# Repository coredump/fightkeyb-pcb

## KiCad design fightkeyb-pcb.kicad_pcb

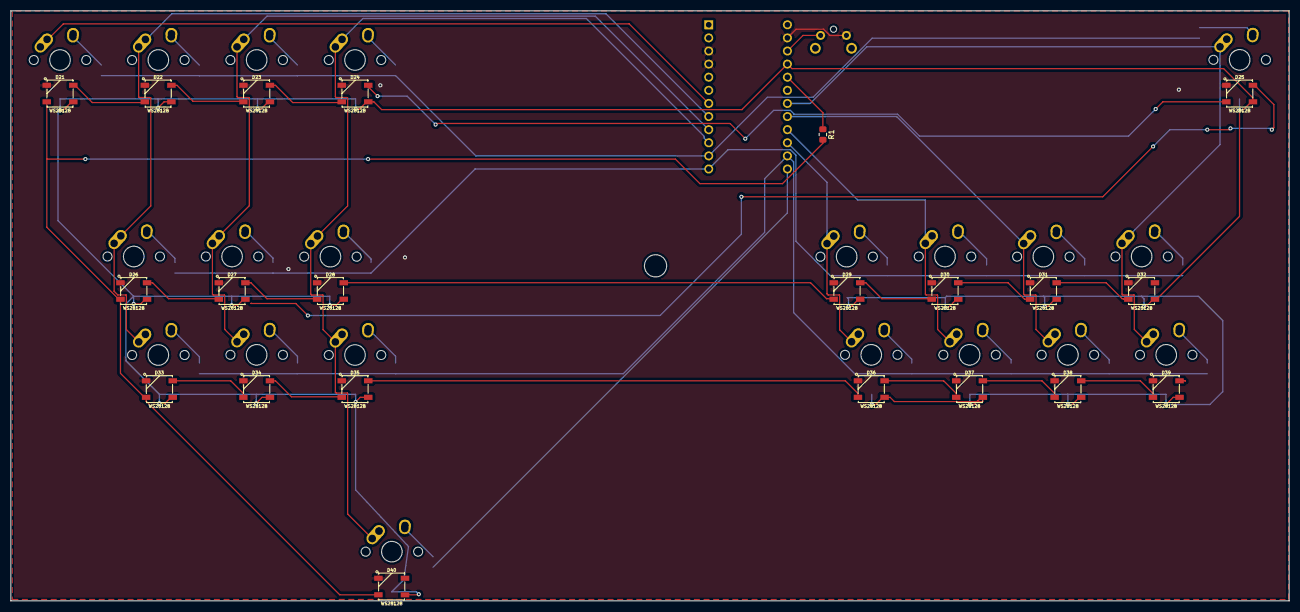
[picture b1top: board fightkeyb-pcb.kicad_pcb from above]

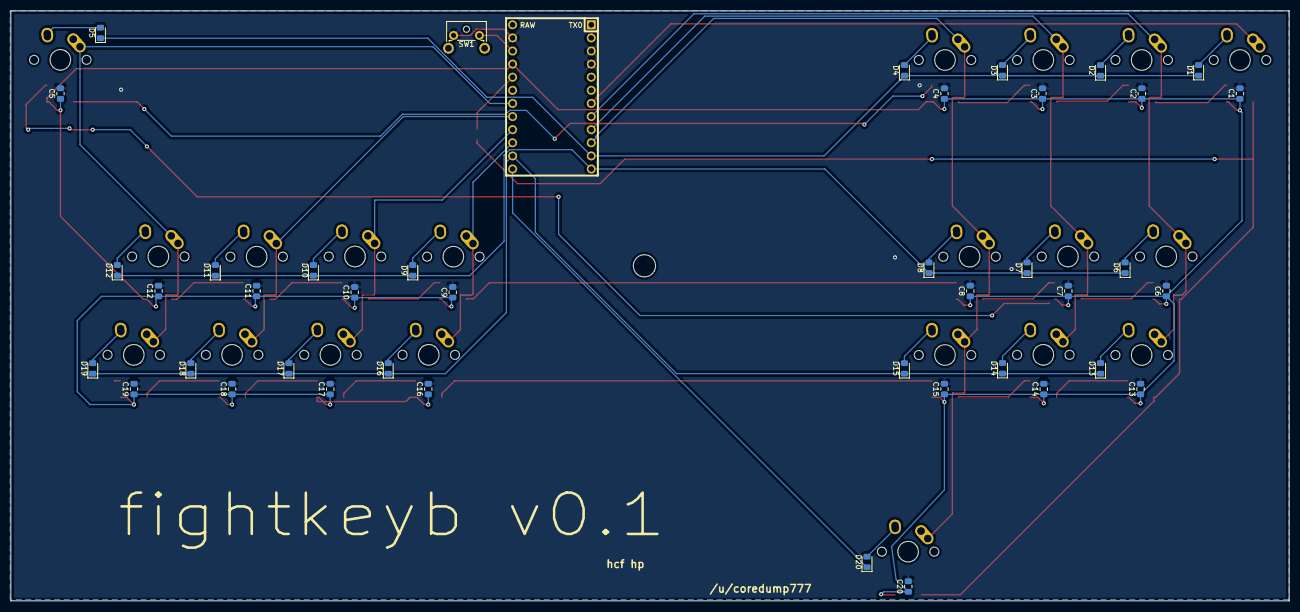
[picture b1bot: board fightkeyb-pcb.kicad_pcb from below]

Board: 2 copper layers, 247.6 x 114.3 mm, 83 parts (41 on the bottom side), 53 nets.

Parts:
C1, C2, C3, C4, C5, C6, C7, C8, C9, C10, C11, C12, C13, C14, C15, C16, C17, C18, C19, C20: 0u1; C_0805_2012Metric_Pad1.15x1.40mm_HandSolder
D1, D2, D3, D4, D5, D6, D7, D8, D9, D10, D11, D12, D13, D14, D15, D16, D17, D18, D19, D20: 1N4148; D_0805_2012Metric_Pad1.15x1.40mm_HandSolder
D21, D22, D23, D24, D25, D26, D27, D28, D29, D30, D31, D32, D33, D34, D35, D36, D37, D38, D39, D40: WS2812B
MX1, MX2, MX3, MX4, MX5, MX6, MX7, MX8, MX9, MX10, MX11, MX12, MX13, MX14, MX15, MX16, MX17, MX18, MX19, MX20: MX-1U; MX-1U-NoLED
R1: 330R; R_0805_2012Metric_Pad1.15x1.40mm_HandSolder
SW1: SW_SPST; SW_Tactile_SPST_Angled_MJTP1117
U1: ProMicro; ArduinoProMicro-BackSide

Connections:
/Led Matrix/DIN: R1.1, U1.20
/Led Matrix/GND: C1.2, C2.2, C3.2, C4.2, C5.2, C6.2, C7.2, C8.2, C9.2, C10.2, C11.2, C12.2, C13.2, C14.2, C15.2, C16.2, C17.2, C18.2, C19.2, C20.2, D21.3, D22.3, D23.3, D24.3, D25.3, D26.3, D27.3, D28.3, D29.3, D30.3, D31.3, D32.3, D33.3, D34.3, D35.3, D36.3, D37.3, D38.3, D39.3, D40.3, SW1.1, U1.3, U1.4, U1.23
/Led Matrix/VCC: C1.1, C2.1, C3.1, C4.1, C5.1, C6.1, C7.1, C8.1, C9.1, C10.1, C11.1, C12.1, C13.1, C14.1, C15.1, C16.1, C17.1, C18.1, C19.1, C20.1, D21.1, D22.1, D23.1, D24.1, D25.1, D26.1, D27.1, D28.1, D29.1, D30.1, D31.1, D32.1, D33.1, D34.1, D35.1, D36.1, D37.1, D38.1, D39.1, D40.1, U1.21
unnamed: D1.1, D2.1, D3.1, D4.1, D5.1, U1.11
unnamed: D1.2, MX1.2
unnamed: D2.2, MX2.2
unnamed: D3.2, MX3.2
unnamed: D4.2, MX4.2
unnamed: D5.2, MX5.2
unnamed: D6.2, MX6.2
unnamed: D7.2, MX7.2
unnamed: D8.2, MX8.2
unnamed: D9.2, MX9.2
unnamed: D6.1, D7.1, D8.1, D9.1, D10.1, D11.1, D12.1, U1.12
unnamed: D10.2, MX10.2
unnamed: D11.2, MX11.2
unnamed: D12.2, MX12.2
unnamed: D13.1, D14.1, D15.1, D16.1, D17.1, D18.1, D19.1, U1.14
unnamed: D13.2, MX13.2
unnamed: D14.2, MX14.2
unnamed: D15.2, MX15.2
unnamed: D16.2, MX16.2
unnamed: D17.2, MX17.2
unnamed: D18.2, MX18.2
unnamed: D19.2, MX19.2
unnamed: D20.1, U1.13
unnamed: D20.2, MX20.2
unnamed: D21.2, D22.4
unnamed: D21.4, D26.4, D33.4, D40.4, R1.2
unnamed: D22.2, D23.4
unnamed: D23.2, D24.4
unnamed: D24.2, D25.4
unnamed: D26.2, D27.4
unnamed: D27.2, D28.4
unnamed: D28.2, D29.4
unnamed: D29.2, D30.4
unnamed: D30.2, D31.4
unnamed: D31.2, D32.4
unnamed: D33.2, D34.4
unnamed: D34.2, D35.4
unnamed: D35.2, D36.4
unnamed: D36.2, D37.4
unnamed: D37.2, D38.4
unnamed: D38.2, D39.4
unnamed: MX1.1, U1.7
unnamed: MX10.1, MX17.1, U1.16
unnamed: MX11.1, MX18.1, U1.17
unnamed: MX5.1, MX12.1, MX19.1, U1.18
unnamed: MX2.1, MX6.1, MX13.1, U1.8
unnamed: MX3.1, MX7.1, MX14.1, U1.9
unnamed: MX4.1, MX8.1, MX15.1, MX20.1, U1.10
unnamed: MX9.1, MX16.1, U1.15
unnamed: SW1.2, U1.22

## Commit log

2018-11-29 Finished new v0.1
2018-11-30 Before trying a reroute
2018-12-01 Finished first production test
2018-12-01 Sent to jlcpcb
